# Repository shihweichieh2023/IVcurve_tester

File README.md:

# I-V Curve Analyzer

A versatile measurement tool for characterizing low-power energy sources, with a focus on Dye-Sensitized Solar Cells (DSSC) and other experimental photovoltaic devices. This open hardware project uses an ESP32-S3 Mini to provide accurate I-V curve measurements and real-time Maximum Power Point tracking.

Originally developed for DIYbio and Hackteria workshops, this analyzer is perfect for:

- Testing Dye-Sensitized Solar Cells (DSSC) with natural dyes
- Characterizing small commercial solar cells
- Evaluating thermoelectric generators (TEGs)
- Educational demonstrations of photovoltaic principles
- Rapid prototyping of new energy harvesting devices

The logarithmic resistor array and optional MOSFET configuration allow measurements across a wide range of power outputs, from µW to mW scale, making it ideal for testing experimental and low-power energy sources.

## Features

- Real-time I-V curve measurement
- Maximum Power Point (MPP) tracking
- OLED display with live readings
- E-ink display for persistent measurements
- Logarithmic resistor array for wide measurement range
- Optional MOSFET for low-resistance measurements
- Built-in voltage divider for measuring higher voltage sources (>3.3V)

## Button Control
The device features a single button for measurement control:

- OLED display: continously provides real-time measurement data
- Single press: Initiates a new I-V curve measurement to be displayed on the E-ink display and sent to the serial.

## Example I-V Curve

The analyzer measures both the I-V characteristics (blue curve) and power output (red curve) by sweeping through different load resistances. The Maximum Power Point (MPP) represents the optimal operating point where the product of voltage and current yields the highest power output.

## E-Ink Display Interface
The analyzer features a 2.9" tri-color (black, white, and red) e-ink display (Adafruit IL0373) for persistent measurement visualization. The e-ink display offers:

- High contrast, daylight-readable display
- Persistent display of measurements even when powered off
- 296x128 pixel resolution
- Low power consumption
- E-ink display: Shows the I-V curve with key measurements (Voc, Isc, MPP) 
- The previous measurement is displayed too in lower contrast to compare

The e-ink display provides a persistent view of your latest results that remains visible even when the device is powered off.

*The e-ink display shows the current measurement in dark contrast while the previous measurement is shown in lighter contrast for easy comparison.*

## Web Interface

The web interface provides real-time visualization of measurements, displaying both the I-V curve (blue) and power curve (pink). Key measurements like Maximum Power Point (MPP), Short Circuit Current (Isc), and Open Circuit Voltage (Voc) are shown in an easy-to-read card layout.

## Hardware Overview
```ascii
+-------------+     +----------+     +-----------+
|  Solar      |     | Resistor |     |    MUX    |
|  Cell       |---->|  Array   |---->|  CD74HC   |
| (DUT)       |     | (R1-R16) |     |   4067    |
+-------------+     +----------+     +-----------+
       |                                  |
       |                                  |
       |                                  |
       |           +---------+            |
       +---------->| MOSFET  |            v
       |           | Circuit |           GND
       |           +---------+            
       |                |                 
       |                |                 
       |                |                 
       |                |        +--------------+
       +----------------+------->|  ESP32-S3    |
                                 |    Mini      |
                                 |   (ADC1)     |
                                 +--------------+
                                      ^
                                      |
                                      |
                                +---------------+
                                | UI Controls   |
                                | OLED, Pots,   |
                                | Button,E-ink  |
                                +---------------+
```

## Key Components

- ESP32-S3 Mini
- CD74HC4067 16-channel multiplexer
- SSD1306 OLED display
- 16 precision resistors (83Ω - 10.3kΩ)
- MOSFET for low-resistance measurements

## Technical Notes
### Resistance Measurement Accuracy
The CD74HC4067 multiplexer has a significant internal ON resistance (RON) of approximately 70Ω that affects measurements. Rather than compensating for this in software, we've directly measured each resistor through the MUX circuit. The resistor values listed in the code (83Ω - 10.3kΩ) already include this MUX internal resistance, ensuring accurate current calculations without additional compensation.

For example:
 
- A 13Ω resistor + ~70Ω MUX RON = 83Ω actual measured value
- This combined resistance is what's stored in the code
- No additional software compensation needed
- Measurements remain accurate across the full range

## Getting Started
1. Clone this repository
2. Install PlatformIO
3. Connect hardware according to [hardware/HARDWARE.md](hardware/HARDWARE.md)
4. Build and upload using PlatformIO

## License
MIT License - See [LICENSE](LICENSE) file

## More Information
See [hardware/HARDWARE.md](hardware/HARDWARE.md) for detailed wiring and setup instructions.

## PCB Design and Prototypes
The project includes a custom PCB design for a MUX ADG706 for more reliable measurements and compact implementation. Design files and documentation can be found in:
 
- Hardware documentation: [`hardware/HARDWARE.md`](hardware/HARDWARE.md)
- PCB design files: [`hardware/MUX-ADG706/`](hardware/MUX-ADG706/)
- PCB renders: [`images/pcb/`](images/pcb/)
- Prototype photos: [`images/prototype/`](images/prototype/)

*Close-up view of the analyzer displaying real-time measurements on the OLED screen. The device shows voltage, current, and power readings while performing I-V curve analysis.*

*First prototype of the I-V Curve Analyzer testing a series of Dye-Sensitized Solar Cells (DSSC). The compact design allows for easy in-line measurements during workshops and experiments.*

### Component Library
The [`ad706/`](MUX-ADG706/ad706/) directory contains all necessary files for the ADG706 multiplexer:

- [`ADG706BRUZ-REEL7.kicad_sym`](MUX-ADG706/ad706/ADG706BRUZ-REEL7.kicad_sym) - KiCad symbol file
- [`SOP65P640X120-28N.kicad_mod`](MUX-ADG706/ad706/SOP65P640X120-28N.kicad_mod) - Footprint for the 28-pin SOP package
- [`ADG706BRUZ-REEL7.step`](MUX-ADG706/ad706/ADG706BRUZ-REEL7.step) - 3D model for visualization

### Project Files
The KiCad project (`MUX-ADG706/`) contains:

- [`MUX-ADG706_v2.kicad_sch`](MUX-ADG706/MUX-ADG706_v2.kicad_sch) - Complete circuit schematic
- [`MUX-ADG706_v2.kicad_pcb`](MUX-ADG706/MUX-ADG706_v2.kicad_pcb) - PCB layout design
- [`gerber_MUX-ADG706_v2.zip`](MUX-ADG706/gerber_MUX-ADG706_v2.zip) - Gerber files for PCB manufacturing

## Credits
Code and hardware design by Marc Dusseiller (@dusjagr), with assistance from the Windsurf AI coding assistant. This collaboration demonstrates how AI tools can enhance open hardware development while maintaining human creativity and expertise at the core of the project.

## References
- I-V curve image from [PVEducation.org](https://www.pveducation.org/pvcdrom/solar-cell-operation/iv-curve)

## Future Improvements
Future development plans for the I-V Curve Analyzer include:

1. **Enhanced Multiplexer**: Replace the current multiplexer with ADG706 for lower internal resistance, improving measurement accuracy especially in the low-resistance range.

2. **IoT Integration**: Utilize the ESP32's WiFi capabilities to upload measurements to an IoT cloud service for:
   - Remote monitoring and data logging
   - Long-term performance analysis
   - Data sharing and collaboration

3. **On-Board Storage**: Implement measurement storage and numbering on the chip for:
   - Offline data collection
   - Sequential measurement tracking
   - Later retrieval and analysis

These improvements will enhance the device's functionality, usability, and data management capabilities while maintaining its core purpose as an accessible tool for energy harvesting research and education.

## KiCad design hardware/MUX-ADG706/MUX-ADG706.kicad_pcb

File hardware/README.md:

# Hardware Design Files

This directory contains the hardware design files for the I-V Curve Analyzer project, including detailed assembly instructions and PCB design files.

*The e-ink display shows the current measurement in dark contrast while the previous measurement is shown in lighter contrast for easy comparison.*

## Directory Structure

- [`HARDWARE.md`](HARDWARE.md) - Detailed assembly instructions and wiring guide
- [`MUX-ADG706/`](MUX-ADG706/) - KiCad project files for the PCB design of the MUX

## PCB Design Overview

The PCB design is implemented in KiCad and features several key improvements over the prototype version:

### Multiplexer Upgrade
The main improvement is the replacement of the CD74HC4067 with the ADG706BRUZ-REEL7 multiplexer:

- Significantly lower ON resistance (~2.5Ω vs 70Ω in the CD74HC4067)
- Better channel-to-channel matching for more consistent measurements
- 28-pin SOP package for compact board layout

### Project Files
The KiCad project (`MUX-ADG706/`) contains:

- [`MUX-ADG706.kicad_sch`](MUX-ADG706/MUX-ADG706.kicad_sch) - Complete circuit schematic
- [`MUX-ADG706.kicad_pcb`](MUX-ADG706/MUX-ADG706.kicad_pcb) - PCB layout design
- [`gerber_MUX-ADG706.zip`](MUX-ADG706/gerber_MUX-ADG706.zip) - Gerber files for PCB manufacturing

### Component Library
The [`ad706/`](MUX-ADG706/ad706/) directory contains all necessary files for the ADG706 multiplexer:

- [`ADG706BRUZ-REEL7.kicad_sym`](MUX-ADG706/ad706/ADG706BRUZ-REEL7.kicad_sym) - KiCad symbol file
- [`SOP65P640X120-28N.kicad_mod`](MUX-ADG706/ad706/SOP65P640X120-28N.kicad_mod) - Footprint for the 28-pin SOP package
- [`ADG706BRUZ-REEL7.step`](MUX-ADG706/ad706/ADG706BRUZ-REEL7.step) - 3D model for visualization

## Design Goals

1. Improve measurement accuracy through lower multiplexer resistance
2. Maintain compact form factor
3. Ensure reliable connections for workshop use
4. Enable precise I-V curve measurements for solar cells and other low-power sources
5. Provide persistent measurement display through e-ink technology

## Display System

The device features a dual-display system:
- **OLED Display**: For real-time measurement data and device status
- **E-ink Display (2.9" Adafruit IL0373)**: For persistent measurement visualization
  - Shows current and previous I-V curves for comparison
  - Maintains display even when powered off
  - High contrast for outdoor readability

## Future Considerations

- Consider adding test points for easier debugging
- Evaluate thermal considerations for continuous operation
- Explore data logging capabilities for long-term studies

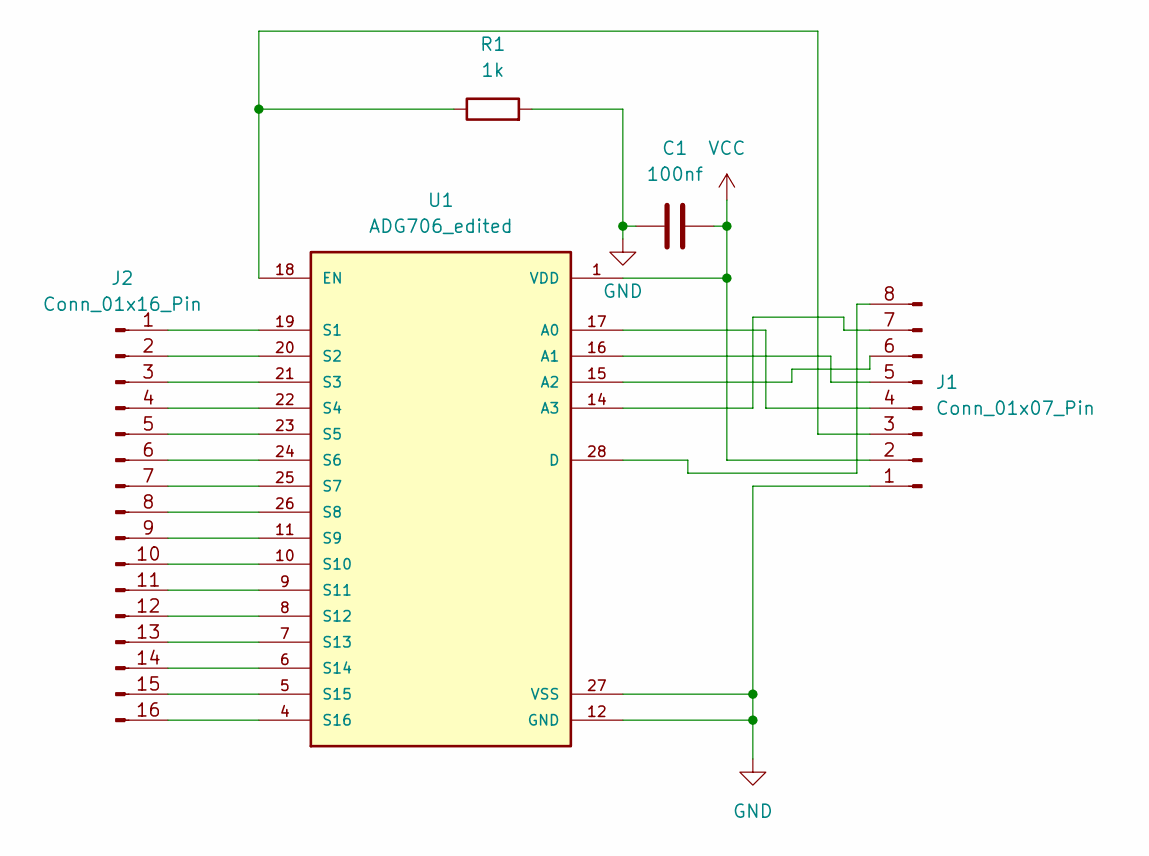
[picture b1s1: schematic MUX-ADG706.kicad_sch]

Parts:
C1: 100nf; C_1210_noGND
J1: Conn_01x07_Pin; PinHeader_1x08_P2.54mm_bigPads
J2: Conn_01x16_Pin; PinHeader_1x16_P2.54mm_bigPads
R1: 1k; R_1206_noGND
U1: ADG706_edited; ADG704-28N

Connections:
GND: C1.1, J1.1, R1.2, U1.12 (GND), U1.27 (VSS)
unnamed: J1.3, R1.1, U1.18 (EN)
unnamed: J1.4, U1.17 (A0)
unnamed: J1.5, U1.16 (A1)
unnamed: J1.6, U1.15 (A2)
unnamed: J1.7, U1.14 (A3)
unnamed: J1.8, U1.28 (D)
unnamed: J2.16 (9), U1.4 (S16)
unnamed: J2.1, U1.19 (S1)
unnamed: J2.2, U1.20 (S2)
unnamed: J2.3, U1.21 (S3)
unnamed: J2.4, U1.22 (S4)
unnamed: J2.5, U1.23 (S5)
unnamed: J2.6, U1.24 (S6)
unnamed: J2.7, U1.25 (S7)
unnamed: J2.8, U1.26 (S8)
unnamed: J2.9, U1.11 (S9)
unnamed: J2.10, U1.10 (S10)
unnamed: J2.11, U1.9 (S11)
unnamed: J2.12, U1.8 (S12)
unnamed: J2.13, U1.7 (S13)
unnamed: J2.14, U1.6 (S14)
unnamed: J2.15, U1.5 (S15)
VCC: C1.2, J1.2, U1.1 (VDD)

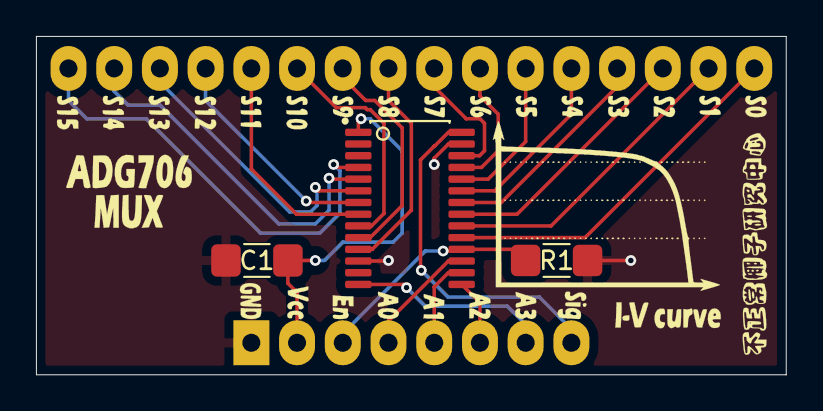
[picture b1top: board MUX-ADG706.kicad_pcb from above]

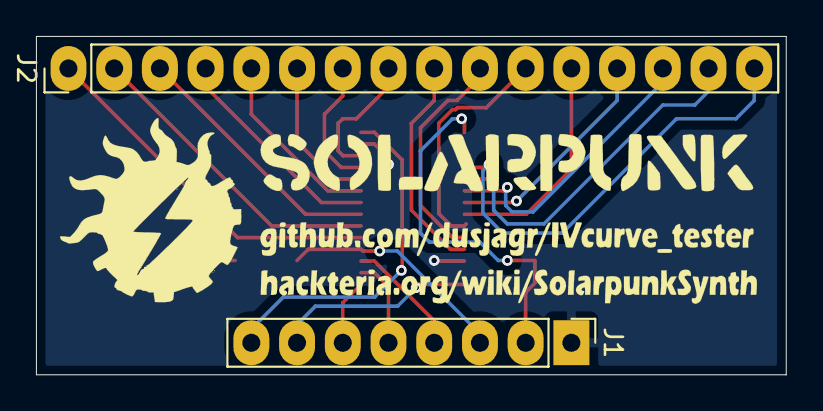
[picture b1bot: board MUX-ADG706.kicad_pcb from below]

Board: 2 copper layers, 41.7 x 18.8 mm, 7 parts (2 on the bottom side), 24 nets.

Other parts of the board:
Ref**: Val**; Back_silkscreen
Ref**#2: Val**; silkscreen

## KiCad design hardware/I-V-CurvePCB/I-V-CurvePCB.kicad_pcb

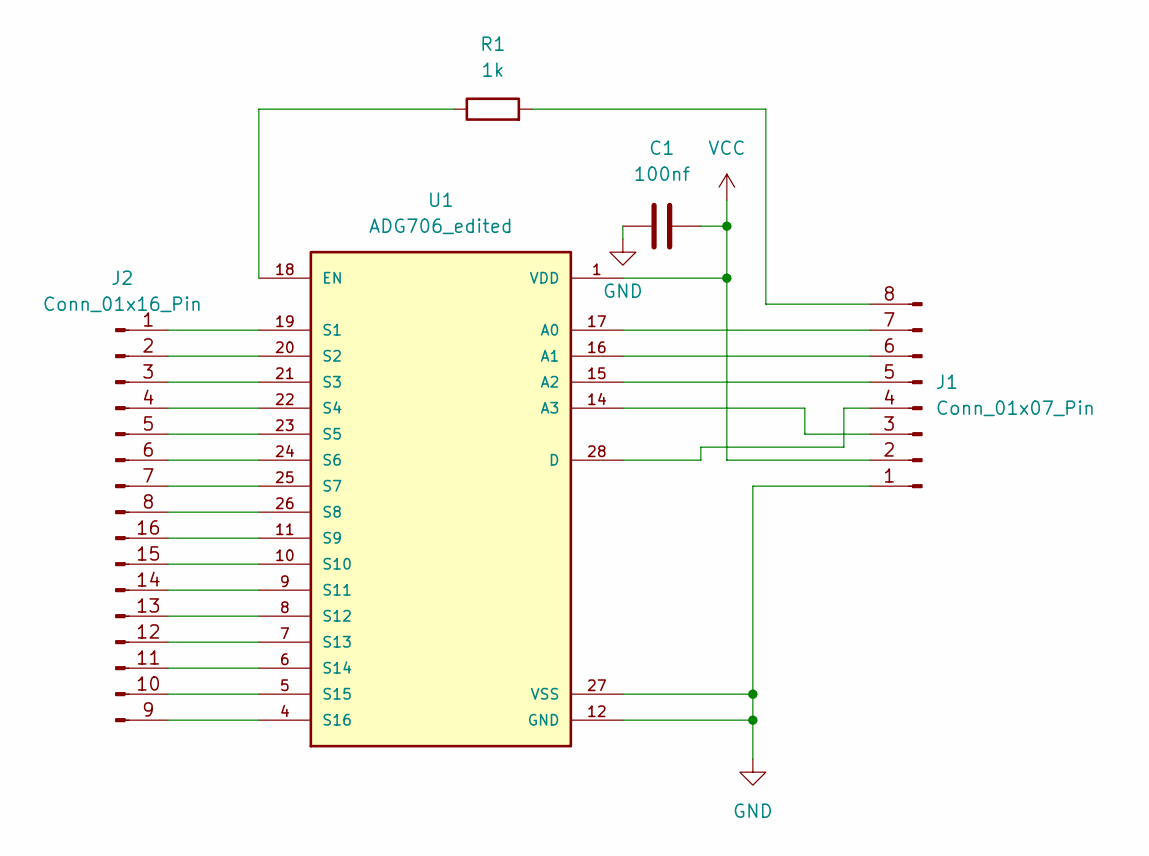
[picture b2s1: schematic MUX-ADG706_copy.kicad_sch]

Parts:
C1: 100nf; C_1210_noGND
J1: Conn_01x07_Pin; PinHeader_1x08_P2.54mm_bigPads
J2: Conn_01x16_Pin; PinHeader_1x16_P2.54mm_bigPads
R1: 1k; R_1206_noGND
U1: ADG706_edited; ADG704-28N

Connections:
GND: C1.1, J1.1, U1.12 (GND), U1.27 (VSS)
unnamed: J1.3, U1.14 (A3)
unnamed: J1.4, U1.28 (D)
unnamed: J1.5, U1.15 (A2)
unnamed: J1.6, U1.16 (A1)
unnamed: J1.7, U1.17 (A0)
unnamed: J1.8, R1.2
unnamed: J2.1, U1.19 (S1)
unnamed: J2.2, U1.20 (S2)
unnamed: J2.3, U1.21 (S3)
unnamed: J2.4, U1.22 (S4)
unnamed: J2.5, U1.23 (S5)
unnamed: J2.6, U1.24 (S6)
unnamed: J2.7, U1.25 (S7)
unnamed: J2.8, U1.26 (S8)
unnamed: J2.16 (Pin_9), U1.11 (S9)
unnamed: J2.15 (Pin_10), U1.10 (S10)
unnamed: J2.14 (Pin_11), U1.9 (S11)
unnamed: J2.13 (Pin_12), U1.8 (S12)
unnamed: J2.12 (Pin_13), U1.7 (S13)
unnamed: J2.11 (Pin_14), U1.6 (S14)
unnamed: J2.10 (Pin_15), U1.5 (S15)
unnamed: R1.1, U1.18 (EN)
unnamed: J2.9, U1.4 (S16)
VCC: C1.2, J1.2, U1.1 (VDD)

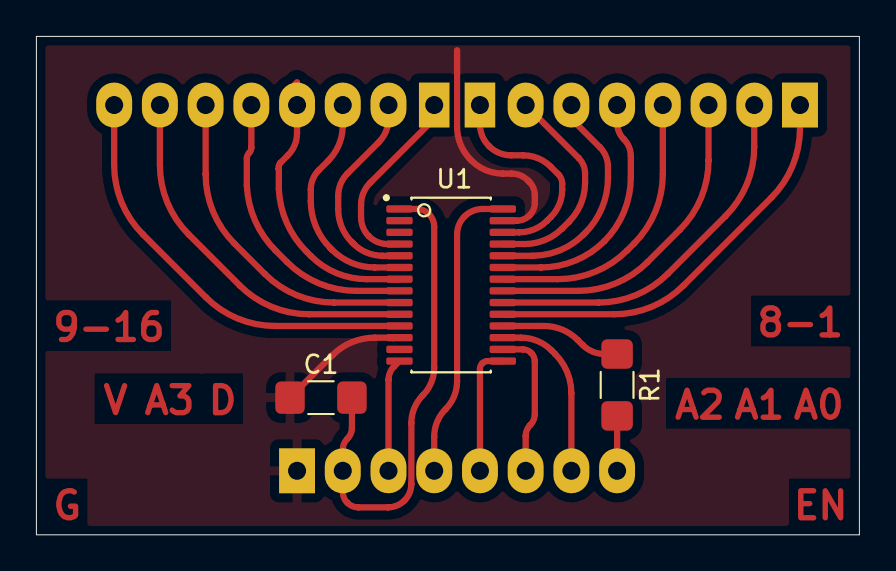
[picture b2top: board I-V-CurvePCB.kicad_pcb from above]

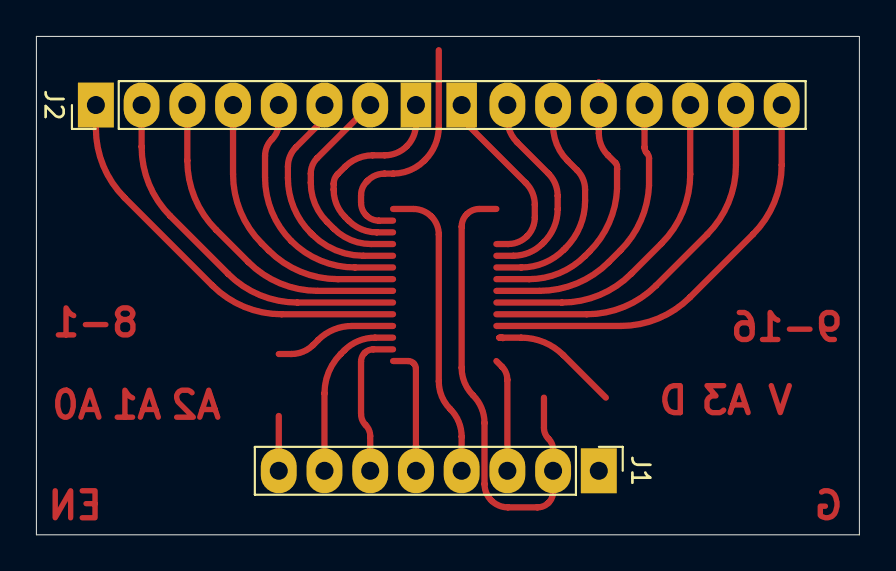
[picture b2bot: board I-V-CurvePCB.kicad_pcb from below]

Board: 2 copper layers, 45.7 x 27.7 mm, 5 parts (2 on the bottom side), 25 nets.

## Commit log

2025-02-01 Initial commit: I-V curve analyzer with ESP32-S3 Mini
2025-02-01 Add MIT License
2025-02-01 Add empty project directories
2025-02-01 Add comprehensive README with DSSC context, MUX details and credits
2025-02-01 Add example I-V curve image with MPP explanation
2025-02-01 Document voltage divider and update block diagram
2025-02-01 Update hardware diagram with improved layout and connections
2025-02-01 Update HARDWARE.md with improved block diagram layout
2025-02-01 Add generated I-V curve example and generation script
2025-02-01 Fix I-V curve image path and update description
2025-02-01 Update I-V curve plot to show power curve and MPP correctly
2025-02-01 Adjust y-axis scales to better position power curve
2025-02-01 Replace generated I-V curve with typical solar cell curve image
2025-02-01 Update README with I-V curve image credits
2025-02-01 Fix markdown formatting in HARDWARE.md for better ASCII art display
2025-02-01 Add voltage divider information to documentation
2025-02-02 Update hardware documentation
2025-02-02 docs: reorganize documentation and add prototype photos
    - Move HARDWARE.md to hardware/ directory
    - Add prototype photos in images/prototype/
    - Fix markdown formatting in README.md
    - Update documentation structure and links
2025-02-02 docs: add hardware README with PCB design documentation
    - Add detailed overview of PCB design improvements
    - Document ADG706 multiplexer upgrade
    - Add file structure and component documentation
    - Include links to all relevant files
2025-02-02 Enhanced boot screens: Added multiple splash screens with improved layout and credits
2025-02-02 Update boot screen year to 2025, add delayLoop variable, remove unused drawIVline1
2025-02-02 Display improvements: Show Voc instead of mV, display maxVoltage in real-time, add delayLoop variable
2025-02-02 Improve code documentation: Add comprehensive comments for hardware setup, pin definitions, measurements, and display functions. Restore I2C pin definitions.
2025-02-11 new mux
2025-02-12 Update firmware and hardware: - Add voltage scaling and MPP calculations - Improve web interface display units - Update KiCad files for ADG706 design - Update .gitignore for KiCad projects
2025-02-12 Add board configuration system: - Create board_config.h for ESP32-S3 Mini and ESP32-C3 Super Mini - Update pin assignments for both boards - Move configuration to src directory - Update hardware docu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
2025-02-12 Move VS Code workspace file to root directory
2025-02-12 Include gerber files for open hardware manufacturing
2025-02-12 Remove old workspace file from src directory (moved to root)
2025-02-12 Remove KiCad backup files from git tracking (kept locally)
2025-02-12 Add support for open WiFi networks: - Create config.template.h for reference - Update WiFi connection code to handle networks without passwords
2025-02-13 Add backup directory to gitignore
2025-02-13 Enhanced web interface and OLED display: - Improved measurement display styling - Fixed units (V, mA, mW) - Removed power axis grid lines - Added screenshot
2025-02-13 docs: Add web interface screenshot to README
2025-02-13 ui: Improve graph display - Reduce container width to 600px - Connect power curve to origin for complete visualization
2025-02-17 Added resistor correction factor to improve current measurements
2025-02-17 Updated configuration and header files
2025-02-17 Improvements: voltage divider fix, power curve display, timing adjustments
    - Fix voltage reading by multiplying by 2 for voltage divider
    - Use dashed lines for previous power curve only
    - Fix array bounds in power curve drawing loops
    - Adjust averaging and timing parameters
    - Improve OLED display formatting for MPP values
2025-02-17 docs: add e-ink display documentation and button functionality to README
2025-02-17 update documentation files about the e-ink display
2025-02-17 deleting unneeded files
2025-02-18 nicer photos
2025-02-28 better defines for eink
2025-03-01 Fix MPP display: Use voltage and current values at maximum power point instead of absolute maximums
2025-03-01 updated readme for new MUX and ADS1115
2025-03-02 minor fixed on the diplay and label axes
2025-03-02 different wifi options
2025-03-03 adding iot data sent to thingspeak
2025-03-04 matlab code for iv curve
2025-03-06 Update IV server data handling and gitignore
2025-08-15 Add Max/MSP integration and enhance IV server API
    ✨ New Features:
    - Add Max/MSP integration folder with patches for real-time IV curve visualization
    - New text-based API endpoints for better data export:
    • /voltage.txt - CSV voltage measurements
    • /current.txt - CSV current measurements
    • /power.txt - CSV power calculations
2025-08-15 Fix Max/MSP JavaScript Rs calculation and outlet order
    - Fix abnormal Rs calculation (was showing -7420Ω, now shows reasonable values)
    - Correct outlet order to match specification:
    • Outlet 0: F_ohmic [FF, Vmpp/Voc, Impp/Isc, Rs, Rsh, curvature, area]
    • Outlet 1: F_dimless [FF, Vmpp/Voc, Impp/Isc, rs, rsh, curvature, area]
    • Outlet 2: basics [Voc, Isc, Vmpp, Impp]
    • Outlet 3: norm_64_curve [Vn0, In0, Vn1, In1, ...]
